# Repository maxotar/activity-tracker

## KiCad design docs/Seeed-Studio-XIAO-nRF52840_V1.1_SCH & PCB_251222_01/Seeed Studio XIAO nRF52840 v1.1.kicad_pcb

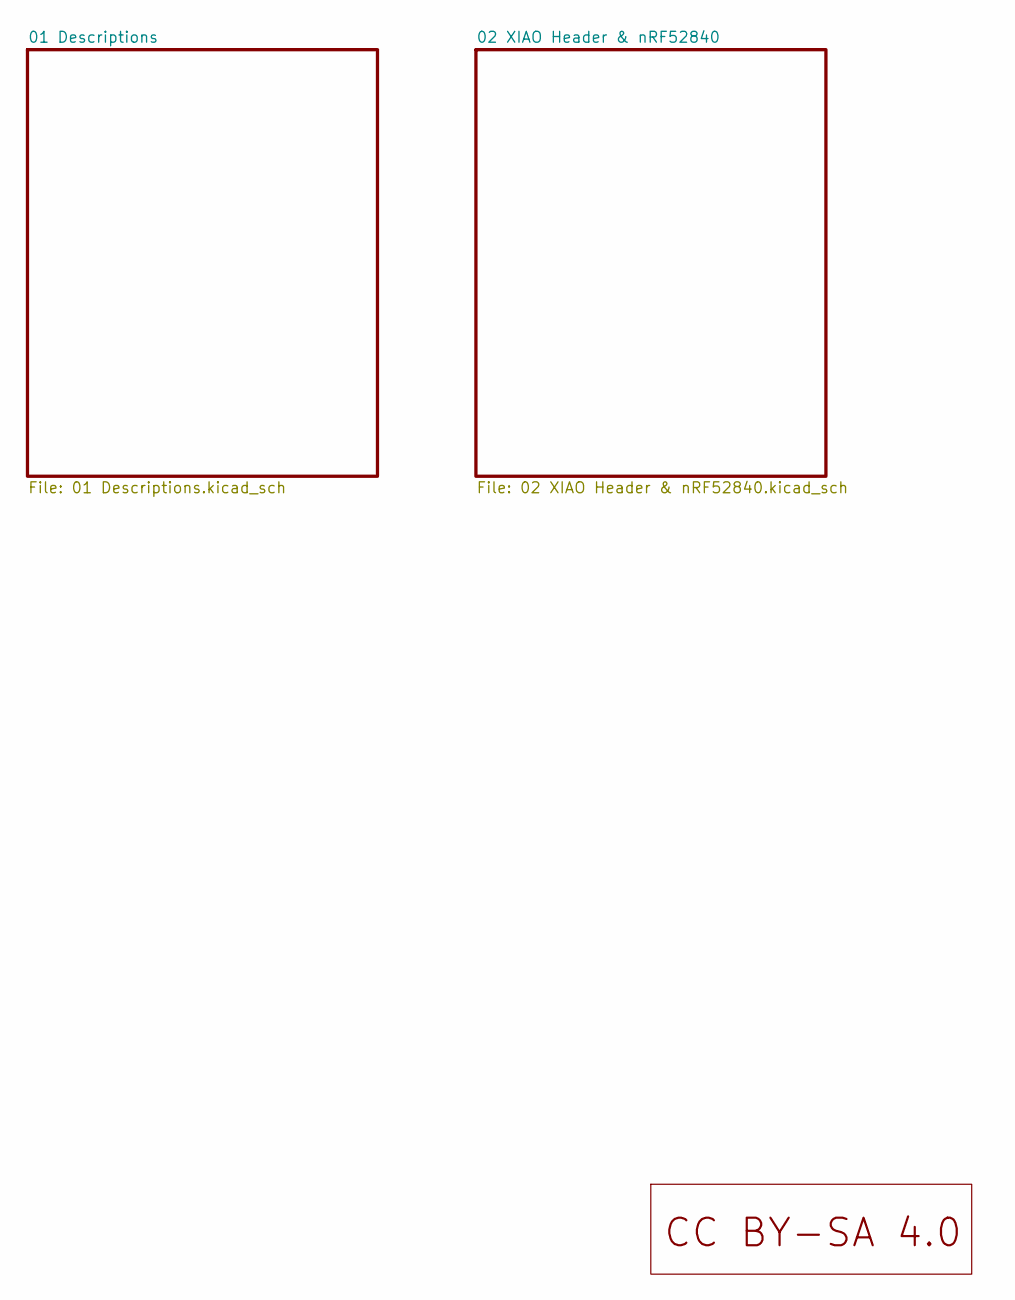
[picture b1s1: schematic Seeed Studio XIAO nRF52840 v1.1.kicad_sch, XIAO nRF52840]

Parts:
U5: LOGO_CC_BY-SA_4.0

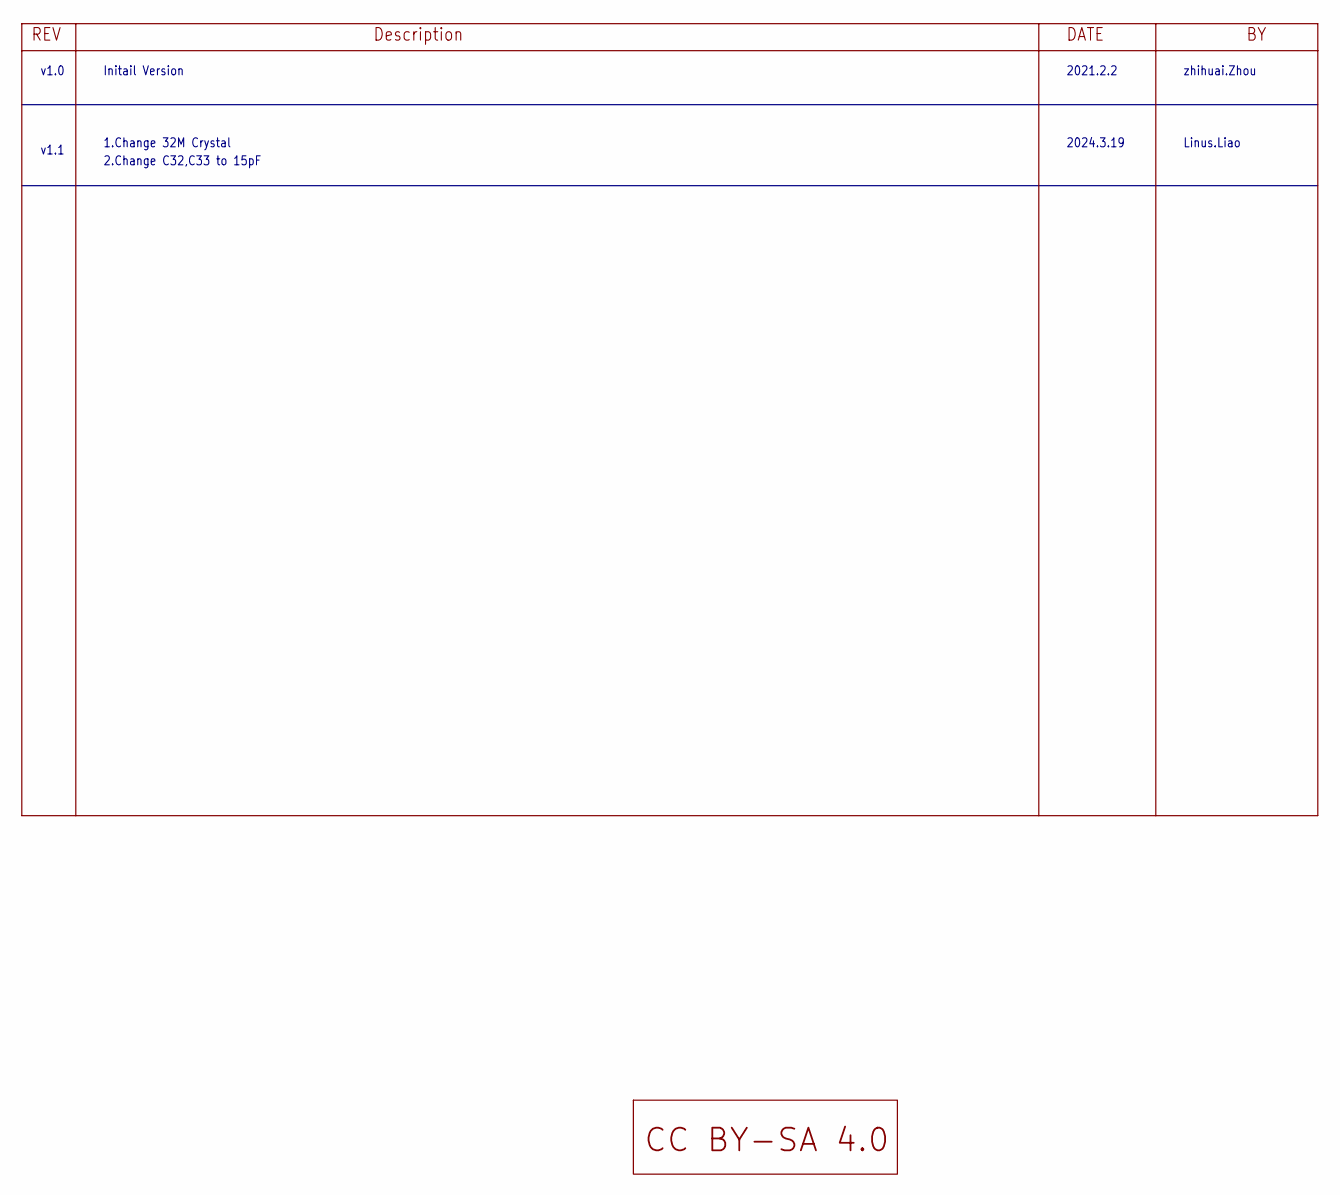
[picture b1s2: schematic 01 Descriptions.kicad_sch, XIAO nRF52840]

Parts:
U8: LOGO_CC_BY-SA_4.0

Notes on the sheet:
zhihuai.Zhou
Linus.Liao
2021.2.2
v1.0
2.Change C32,C33 to 15pF
v1.1
1.Change 32M Crystal
2024.3.19
Initail Version

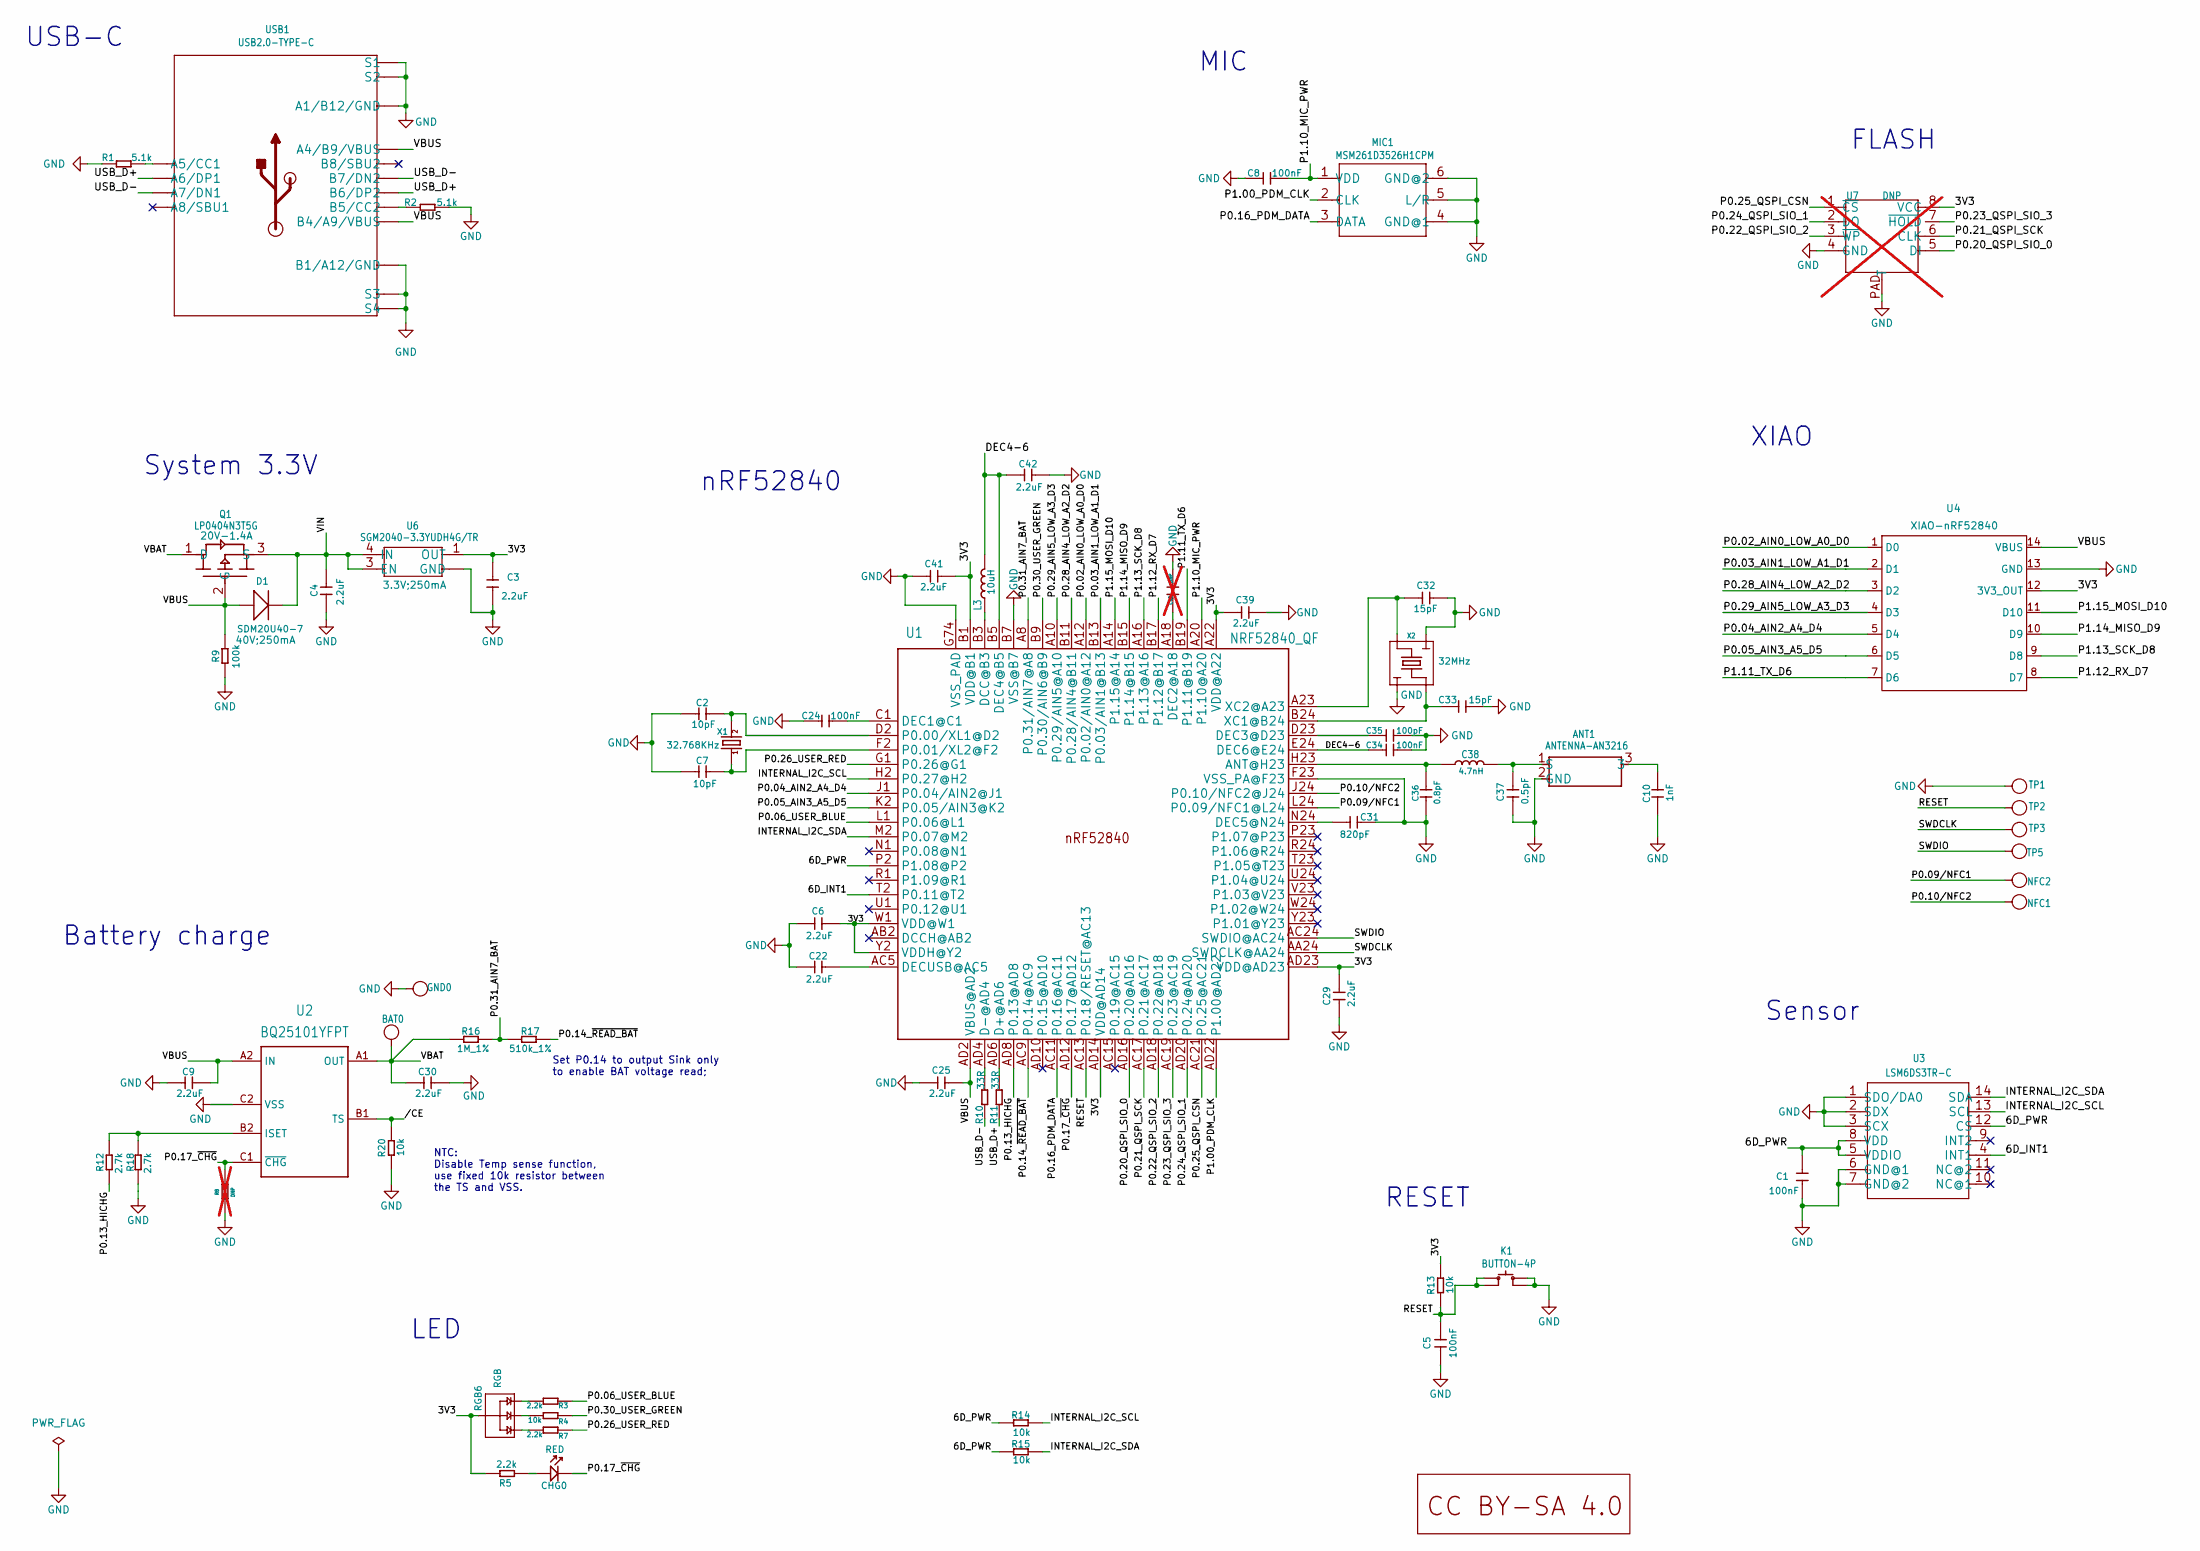
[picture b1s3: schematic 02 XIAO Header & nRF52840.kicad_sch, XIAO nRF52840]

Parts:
ANT1: ANTENNA-AN3216; ANT-SMD3P-3.2X1.6X1.04MM
BAT0: TEST-POINT'4080'; TP-80X40MIL
C1, C5, C8, C24, C34: 100nF; C0201
C2, C7: 10pF; C0201
C3, C4, C6, C9, C22, C25, C29, C30, C39, C41, C42: 2.2uF; C0201
C10: 1nF; C0402
C31: 820pF; C0201
C32, C33: 15pF; C0201
C35: 100pF; C0201
C36: 0.8pF; C0201
C37: 0.5pF; C0201
C38: 4.7nH; L0201
C40: DNP; C0201; not fitted
CHG0: RED; LED-0402
D1: SDM20U40-7; SOD-523
GND0: GND; TP-80X40MIL
K1: BUTTON-4P; SW4-SMD-2.8-2.6X1.6X0.53MM
L3: 10uH; L0603
MIC1: MSM261D3526H1CPM; MIC6P-3.5X2.65X0.94MM
NFC1, NFC2: TEST-POINT'4080'; TP-80X40MIL
Q1: LP0404N3T5G; PMOS_1.0_0.6_0.35MM
R1, R2: 5.1k; R0201
R3, R5, R7: 2.2k; R0201
R4, R13, R14, R15, R20: 10k; R0201
R8: DNP; R0201; not fitted
R9: 100k; R0201
R10, R11: 33R; R0201
R12, R18: 2.7k; R0201
R16: 1M_1%; R0201
R17: 510k_1%; R0201
RGB6: RGB; 4P1010
TP1, TP2, TP3, TP5: TEST-POINT'4545'; TP-D45MIL
U1: NRF52840_QF; AQFN50P700X700X85_HS-74N
U2: BQ25101YFPT; DSBGA6-0.4-1.6x0.9x0.5mm; MPN BQ25101YFPT
U3: LSM6DS3TR-C; LGA14-0.5-2.5X3X0.86MM
U4: XIAO-nRF52840; XIAO-Add-On
U6: SGM2040-3.3YUDH4G/TR; X2SON-4
U7: DNP; USON2X3_8; not fitted
U9: LOGO_CC_BY-SA_4.0
USB1: USB2.0-TYPE-C
X1: 32.768KHz; X2-SMD-L1.6X1.0X0.5MM
X2: 32MHz; 4P1612

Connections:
/02 XIAO Header & nRF52840/3V3: C3.2, C6.2, C29.2, C39.1, C41.2, R5.1, R13.1, RGB6.+, U1.A22 (VDD@A22), U1.AD14 (VDD@AD14), U1.AD23 (VDD@AD23), U1.B1 (VDD@B1), U1.W1 (VDD@W1), U1.Y2 (VDDH@Y2), U4.12 (3V3_OUT), U6.1 (OUT), U7.8 (VCC)
/02 XIAO Header & nRF52840/6D_INT1: U1.T2 (P0.11@T2), U3.4 (INT1)
/02 XIAO Header & nRF52840/6D_PWR: C1.2, R14.1, R15.1, U1.P2 (P1.08@P2), U3.5 (VDDIO), U3.8 (VDD), U3.12 (CS)
/02 XIAO Header & nRF52840/DEC4-6: C34.1, C42.1, L3.2, U1.B5 (DEC4@B5), U1.E24 (DEC6@E24)
/02 XIAO Header & nRF52840/INTERNAL_I2C_SCL: R14.2, U1.H2 (P0.27@H2), U3.13 (SCL)
/02 XIAO Header & nRF52840/INTERNAL_I2C_SDA: R15.2, U1.M2 (P0.07@M2), U3.14 (SDA)
/02 XIAO Header & nRF52840/P0.02_AIN0_LOW_A0_D0: U1.A12 (P0.02/AIN0@A12), U4.1 (D0)
/02 XIAO Header & nRF52840/P0.03_AIN1_LOW_A1_D1: U1.B13 (P0.03/AIN1@B13), U4.2 (D1)
/02 XIAO Header & nRF52840/P0.04_AIN2_A4_D4: U1.J1 (P0.04/AIN2@J1), U4.5 (D4)
/02 XIAO Header & nRF52840/P0.05_AIN3_A5_D5: U1.K2 (P0.05/AIN3@K2), U4.6 (D5)
/02 XIAO Header & nRF52840/P0.06_USER_BLUE: R3.2, U1.L1 (P0.06@L1)
/02 XIAO Header & nRF52840/P0.09/NFC1: NFC2.1 (T), U1.L24 (P0.09/NFC1@L24)
/02 XIAO Header & nRF52840/P0.10/NFC2: NFC1.1 (T), U1.J24 (P0.10/NFC2@J24)
/02 XIAO Header & nRF52840/P0.13_HICHG: R12.2, U1.AD8 (P0.13@AD8)
/02 XIAO Header & nRF52840/P0.14_~READ_BAT: R17.2, U1.AC9 (P0.14@AC9)
/02 XIAO Header & nRF52840/P0.16_PDM_DATA: MIC1.3 (DATA), U1.AC11 (P0.16@AC11)
/02 XIAO Header & nRF52840/P0.17_~CHG: CHG0.-, R8.1, U1.AD12 (P0.17@AD12), U2.C1 (~CHG)
/02 XIAO Header & nRF52840/P0.20_QSPI_SIO_0: U1.AD16 (P0.20@AD16), U7.5 (DI)
/02 XIAO Header & nRF52840/P0.21_QSPI_SCK: U1.AC17 (P0.21@AC17), U7.6 (CLK)
/02 XIAO Header & nRF52840/P0.22_QSPI_SIO_2: U1.AD18 (P0.22@AD18), U7.3 (~WP)
/02 XIAO Header & nRF52840/P0.23_QSPI_SIO_3: U1.AC19 (P0.23@AC19), U7.7 (~HOLD)
/02 XIAO Header & nRF52840/P0.24_QSPI_SIO_1: U1.AD20 (P0.24@AD20), U7.2 (DO)
/02 XIAO Header & nRF52840/P0.25_QSPI_CSN: U1.AC21 (P0.25@AC21), U7.1 (~CS)
/02 XIAO Header & nRF52840/P0.26_USER_RED: R7.2, U1.G1 (P0.26@G1)
/02 XIAO Header & nRF52840/P0.28_AIN4_LOW_A2_D2: U1.B11 (P0.28/AIN4@B11), U4.3 (D2)
/02 XIAO Header & nRF52840/P0.29_AIN5_LOW_A3_D3: U1.A10 (P0.29/AIN5@A10), U4.4 (D3)
/02 XIAO Header & nRF52840/P0.30_USER_GREEN: R4.2, U1.B9 (P0.30/AIN6@B9)
/02 XIAO Header & nRF52840/P0.31_AIN7_BAT: R16.2, R17.1, U1.A8 (P0.31/AIN7@A8)
/02 XIAO Header & nRF52840/P1.00_PDM_CLK: MIC1.2 (CLK), U1.AD22 (P1.00@AD22)
/02 XIAO Header & nRF52840/P1.10_MIC_PWR: C8.2, MIC1.1 (VDD), U1.A20 (P1.10@A20)
/02 XIAO Header & nRF52840/P1.11_TX_D6: U1.B19 (P1.11@B19), U4.7 (D6)
/02 XIAO Header & nRF52840/P1.12_RX_D7: U1.B17 (P1.12@B17), U4.8 (D7)
/02 XIAO Header & nRF52840/P1.13_SCK_D8: U1.A16 (P1.13@A16), U4.9 (D8)
/02 XIAO Header & nRF52840/P1.14_MISO_D9: U1.B15 (P1.14@B15), U4.10 (D9)
/02 XIAO Header & nRF52840/P1.15_MOSI_D10: U1.A14 (P1.15@A14), U4.11 (D10)
/02 XIAO Header & nRF52840/RESET: C5.1, K1.1 (A0), K1.3 (A1), R13.2, TP2.T, U1.AC13 (P0.18/RESET@AC13)
/02 XIAO Header & nRF52840/SWDCLK: TP3.T, U1.AA24 (SWDCLK@AA24)
/02 XIAO Header & nRF52840/SWDIO: TP5.T, U1.AC24 (SWDIO@AC24)
/02 XIAO Header & nRF52840/USB_D+: R11.1, USB1.A6 (A6/DP1), USB1.B6 (B6/DP2)
/02 XIAO Header & nRF52840/USB_D-: R10.1, USB1.A7 (A7/DN1), USB1.B7 (B7/DN2)
/02 XIAO Header & nRF52840/VBAT: BAT0.1 (T), C30.1, Q1.1 (D), R16.1, U2.A1 (OUT)
/02 XIAO Header & nRF52840/VBUS: C9.2, C25.2, D1.+, Q1.2 (G), R9.2, U1.AD2 (VBUS@AD2), U2.A2 (IN), U4.14 (VBUS), USB1.A4_B9 (A4/B9/VBUS), USB1.B4_A9 (B4/A9/VBUS)
/02 XIAO Header & nRF52840/VIN: C4.1, D1.-, Q1.3 (S), U6.3 (EN), U6.4 (IN)
/02 XIAO Header & nRF52840//CE: R20.1, U2.B1 (TS)
GND: ANT1.2 (GND), C1.1, C2.1, C3.1, C4.2, C5.2, C6.1, C7.1, C8.1, C9.1, C10.1, C22.1, C24.1, C25.1, C29.1, C30.2, C31.2, C32.2, C33.2, C34.2, C35.2, C36.1, C37.1, C39.2, C40.2, C41.1, C42.2, GND0.1 (T), K1.2 (B0), K1.4 (B1), MIC1.4 (GND@1), MIC1.5 (L/R), MIC1.6 (GND@2), R1.2, R2.1, R8.2, R9.1, R18.2, R20.2, TP1.T, U1.B7 (VSS@B7), U1.F23 (VSS_PA@F23), U1.G74 (VSS_PAD), U2.C2 (VSS), U3.1 (SDO/DA0), U3.2 (SDX), U3.3 (SCX), U3.6 (GND@1), U3.7 (GND@2), U4.13 (GND), U6.2 (GND), U6.T (GND), U7.4 (GND), U7.PAD (T), USB1.A1_B12 (A1/B12/GND), USB1.B1_A12 (B1/A12/GND), USB1.S1, USB1.S2, USB1.S3, USB1.S4, USB1.S5 (S1), USB1.S6 (S2), X2.2 (1), X2.4 (3)
unnamed: ANT1.3, C10.2
unnamed: ANT1.1 (S), C37.2, C38.2
unnamed: CHG0.+, R5.2
unnamed: R3.1, RGB6.B-
unnamed: R4.1, RGB6.G-
unnamed: R7.1, RGB6.R-
unnamed: C36.2, C38.1, U1.H23 (ANT@H23)
unnamed: R11.2, U1.AD6 (D+@AD6)
unnamed: R10.2, U1.AD4 (D-@AD4)
unnamed: L3.1, U1.B3 (DCC@B3)
unnamed: C24.2, U1.C1 (DEC1@C1)
unnamed: C40.1, U1.A18 (DEC2@A18)
unnamed: C35.1, U1.D23 (DEC3@D23)
unnamed: C31.1, U1.N24 (DEC5@N24)
unnamed: C22.2, U1.AC5 (DECUSB@AC5)
unnamed: C2.2, U1.D2 (P0.00/XL1@D2), X1.2
unnamed: C7.2, U1.F2 (P0.01/XL2@F2), X1.1
unnamed: C33.1, U1.B24 (XC1@B24), X2.1 (2)
unnamed: C32.1, U1.A23 (XC2@A23), X2.3 (4)
unnamed: R12.1, R18.1, U2.B2 (ISET)
unnamed: R1.1, USB1.A5 (A5/CC1)
unnamed: R2.2, USB1.B5 (B5/CC2)

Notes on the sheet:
the TS and VSS.
use fixed 10k resistor between
Battery charge
LED
RESET
Sensor
USB-C
FLASH
nRF52840
XIAO
Set P0.14 to output Sink only to enable BAT voltage read;
System 3.3V
Disable Temp sense function,
NTC:
MIC

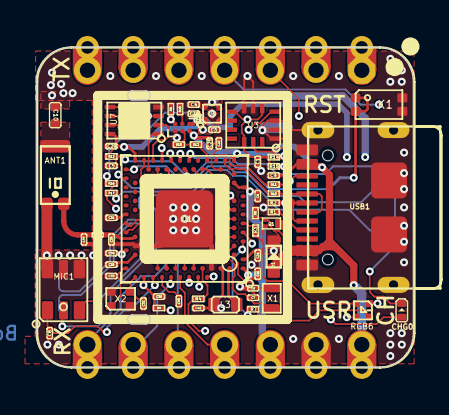
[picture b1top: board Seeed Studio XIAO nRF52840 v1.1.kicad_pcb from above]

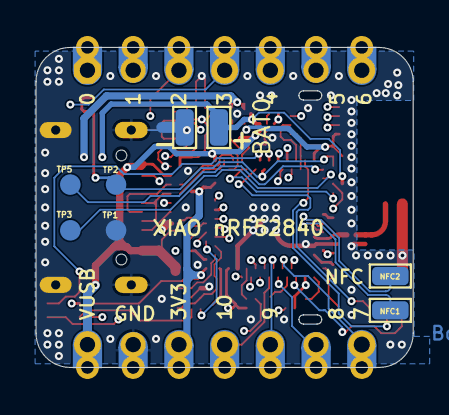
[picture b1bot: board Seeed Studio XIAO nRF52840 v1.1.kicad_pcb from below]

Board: 4 copper layers, 21.0 x 17.8 mm, 73 parts (8 on the bottom side), 67 nets.

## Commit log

2026-02-18 functional BLE LED Blinky
2026-02-18 reporting imu values to serial works
2026-02-18 working connection to adafruit app
2026-03-01 switch to PIO, working IMU reads
2026-03-02 compute useful data, fifo set up, no sleep yet
2026-03-02 interrupt and sleep working
